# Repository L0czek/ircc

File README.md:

# Resonant Converter Controller

This repository contains a work-in-progress resonant converter controller project based on the STM32G474 microcontroller. The system splits responsibilities between the MCU (`controller`) and a host application (`host`) running on an x86 machine for configuration, logging, and waveform retrieval.

**Goals**
- Implement a phase-shifted resonant converter controller using the STM32G474 high-resolution timers.
- Provide over-current and other protections using built-in ADCs and comparator peripherals.
- Log waveforms to local SRAM for later retrieval by the host.
- Provide a PC-side host binary to configure and interact with the MCU.

Repository layout
- [controller](controller): MCU firmware (STM32 HAL-based). Core control logic lives here.
- [host](host): Host-side application that communicates with the MCU (x86 binary).
- [target](target): CubeMX / board-specific projects and HAL integration for different targets/boards.
- [pcb](pcb): KiCad PCB design files for the controller hardware.
- [protocol](protocol): Protocol definitions and protobufs used by host/MCU.
- [external](external): Third-party libraries and dependencies (e.g., nanpb, drivers).
- [build](build): Top-level build artifacts and CMake cache (generated during builds).

Quick start

Build host part (x86):

1. Enter the host directory and create a build directory:

```bash
cd host
mkdir -p build && cd build
cmake ..
make -j
```

The produced host binary will be in `host/build` (or as specified by the host CMakeLists).

Build MCU firmware:

1. Edit or inspect the CubeMX project in the appropriate `target/*` folder (for your chosen board). Generate code from CubeMX if you modify pin/peripheral configuration.
2. Use CMake from the top-level CMake to build the firmware. Example (from project root):

```bash
mkdir -p build-mcu && cd build-mcu
cmake -DCMAKE_TOOLCHAIN_FILE=cmake/gcc-arm-none-eabi.cmake ..
make -j
```

Flashing and debugging
- An OpenOCD config is available at `build/openocd.cfg` for target debugging.
- Typical workflow using the repository make targets:

	1. Start OpenOCD to provide the debug server:

		 ```bash
		 make openocd
		 ```

	2. In a separate terminal, flash or debug the firmware:

		 - To flash and run the firmware:

			 ```bash
			 make run
			 ```

		 - To spawn `gdb` for interactive debugging (connects to the OpenOCD server):

			 ```bash
			 make gdb
			 ```

- Or use your preferred OpenOCD/ST-Link workflow if you have a different setup.

Protocol and message formats
- Communication between host and MCU uses a UART serial link and the message definitions in the [protocol](protocol) directory (protobuf/nanopb). Regenerate or inspect generated code if you change `.proto` files.

Design notes
- The controller firmware uses the STM32G474 high-resolution timers to implement phase-shift control for MOSFET/IGBT bridge switching.
- ADCs, comparators, and timers are used for protections, sampling, and logging to SRAM.

Acknowledgements
- Third-party libraries are located in `external/` — see their respective LICENSE files for details.

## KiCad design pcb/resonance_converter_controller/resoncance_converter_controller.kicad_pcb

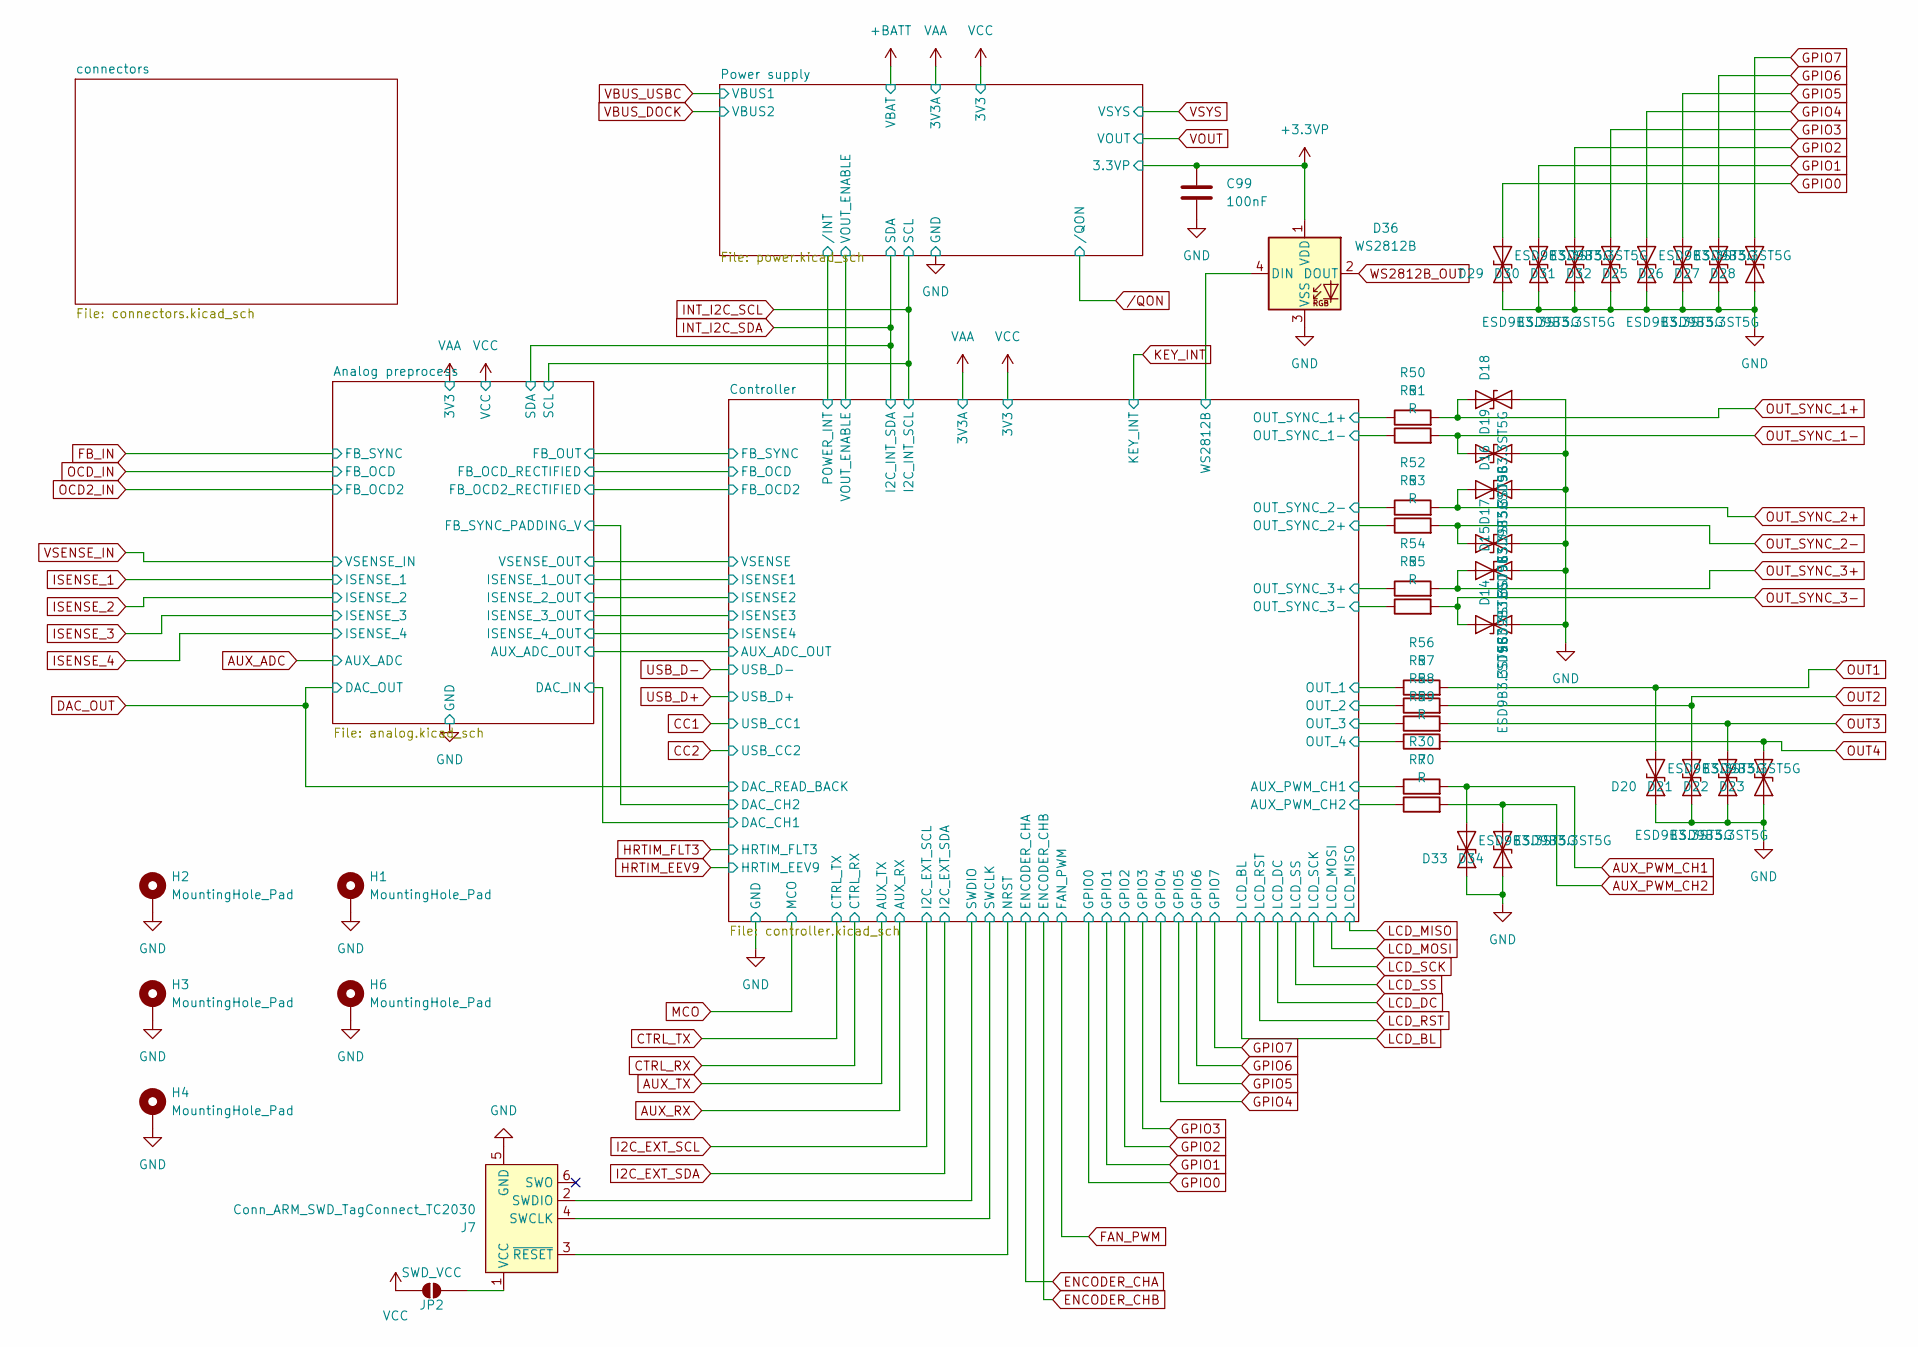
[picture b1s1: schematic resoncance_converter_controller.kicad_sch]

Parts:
C99: 100nF; C_0402_1005Metric
D14, D15, D16, D17, D18, D19, D20, D21, D22, D23, D25, D26, D27, D28, D29, D30, D31, D32, D33, D34: ESD9B3.3ST5G; D_SOD-923
D36: WS2812B; LED_WS2812B-Mini_PLCC4_3.5x3.5mm
H1, H2, H3, H4, H6: MountingHole_Pad; MountingHole_2.2mm_M2_Pad_Via
J7: Conn_ARM_SWD_TagConnect_TC2030; Tag-Connect_TC2030-IDC-FP_2x03_P1.27mm_Vertical
JP2: SWD_VCC; SolderJumper-2_P1.3mm_Open_RoundedPad1.0x1.5mm
R30, R50, R51, R52, R53, R54, R55, R56, R57, R58, R59, R70: R; R_0402_1005Metric

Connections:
+3.3VP: C99.1, D36.1 (VDD); also elsewhere on the board
/Controller/AUX_PWM_CH1: R30.1; also elsewhere on the board
/Controller/AUX_PWM_CH2: R70.1; also elsewhere on the board
/Controller/OUT_1: R56.1; also elsewhere on the board
/Controller/OUT_2: R57.1; also elsewhere on the board
/Controller/OUT_3: R58.1; also elsewhere on the board
/Controller/OUT_4: R59.1; also elsewhere on the board
/Controller/OUT_SYNC_1+: R50.1; also elsewhere on the board
/Controller/OUT_SYNC_1-: R51.1; also elsewhere on the board
/Controller/OUT_SYNC_2+: R53.1; also elsewhere on the board
/Controller/OUT_SYNC_2-: R52.1; also elsewhere on the board
/Controller/OUT_SYNC_3+: R54.1; also elsewhere on the board
/Controller/OUT_SYNC_3-: R55.1; also elsewhere on the board
/Controller/WS2812B: D36.4 (DIN); also elsewhere on the board
AUX_PWM_CH1: D33.1 (A1), R30.2; also elsewhere on the board
AUX_PWM_CH2: D34.1 (A1), R70.2; also elsewhere on the board
GND: C99.2, D14.1 (A1), D15.1 (A1), D16.1 (A1), D17.1 (A1), D18.1 (A1), D19.1 (A1), D20.2 (A2), D21.2 (A2), D22.2 (A2), D23.2 (A2), D25.2 (A2), D26.2 (A2), D27.2 (A2), D28.2 (A2), D29.2 (A2), D30.2 (A2), D31.2 (A2), D32.2 (A2), D33.2 (A2), D34.2 (A2), D36.3 (VSS), H1.1 (1_1), H2.1 (1_1), H3.1 (1_1), H4.1 (1_1), H6.1 (1_1), J7.5 (GND); also elsewhere on the board
GPIO0: D29.1 (A1); also elsewhere on the board
GPIO1: D30.1 (A1); also elsewhere on the board
GPIO2: D31.1 (A1); also elsewhere on the board
GPIO3: D32.1 (A1); also elsewhere on the board
GPIO4: D25.1 (A1); also elsewhere on the board
GPIO5: D26.1 (A1); also elsewhere on the board
GPIO6: D27.1 (A1); also elsewhere on the board
GPIO7: D28.1 (A1); also elsewhere on the board
NRST: J7.3 (~RESET); also elsewhere on the board
unnamed: J7.1 (VCC), JP2.2 (B)
OUT1: D20.1 (A1), R56.2; also elsewhere on the board
OUT2: D21.1 (A1), R57.2; also elsewhere on the board
OUT3: D22.1 (A1), R58.2; also elsewhere on the board
OUT4: D23.1 (A1), R59.2; also elsewhere on the board
OUT_SYNC_1+: D18.2 (A2), R50.2; also elsewhere on the board
OUT_SYNC_1-: D19.2 (A2), R51.2; also elsewhere on the board
OUT_SYNC_2+: D16.2 (A2), R52.2; also elsewhere on the board
OUT_SYNC_2-: D17.2 (A2), R53.2; also elsewhere on the board
OUT_SYNC_3+: D15.2 (A2), R54.2; also elsewhere on the board
OUT_SYNC_3-: D14.2 (A2), R55.2; also elsewhere on the board
SWCLK: J7.4 (SWCLK); also elsewhere on the board
SWDIO: J7.2 (SWDIO); also elsewhere on the board
VCC: JP2.1 (A); also elsewhere on the board
WS2812B_OUT: D36.2 (DOUT); also elsewhere on the board

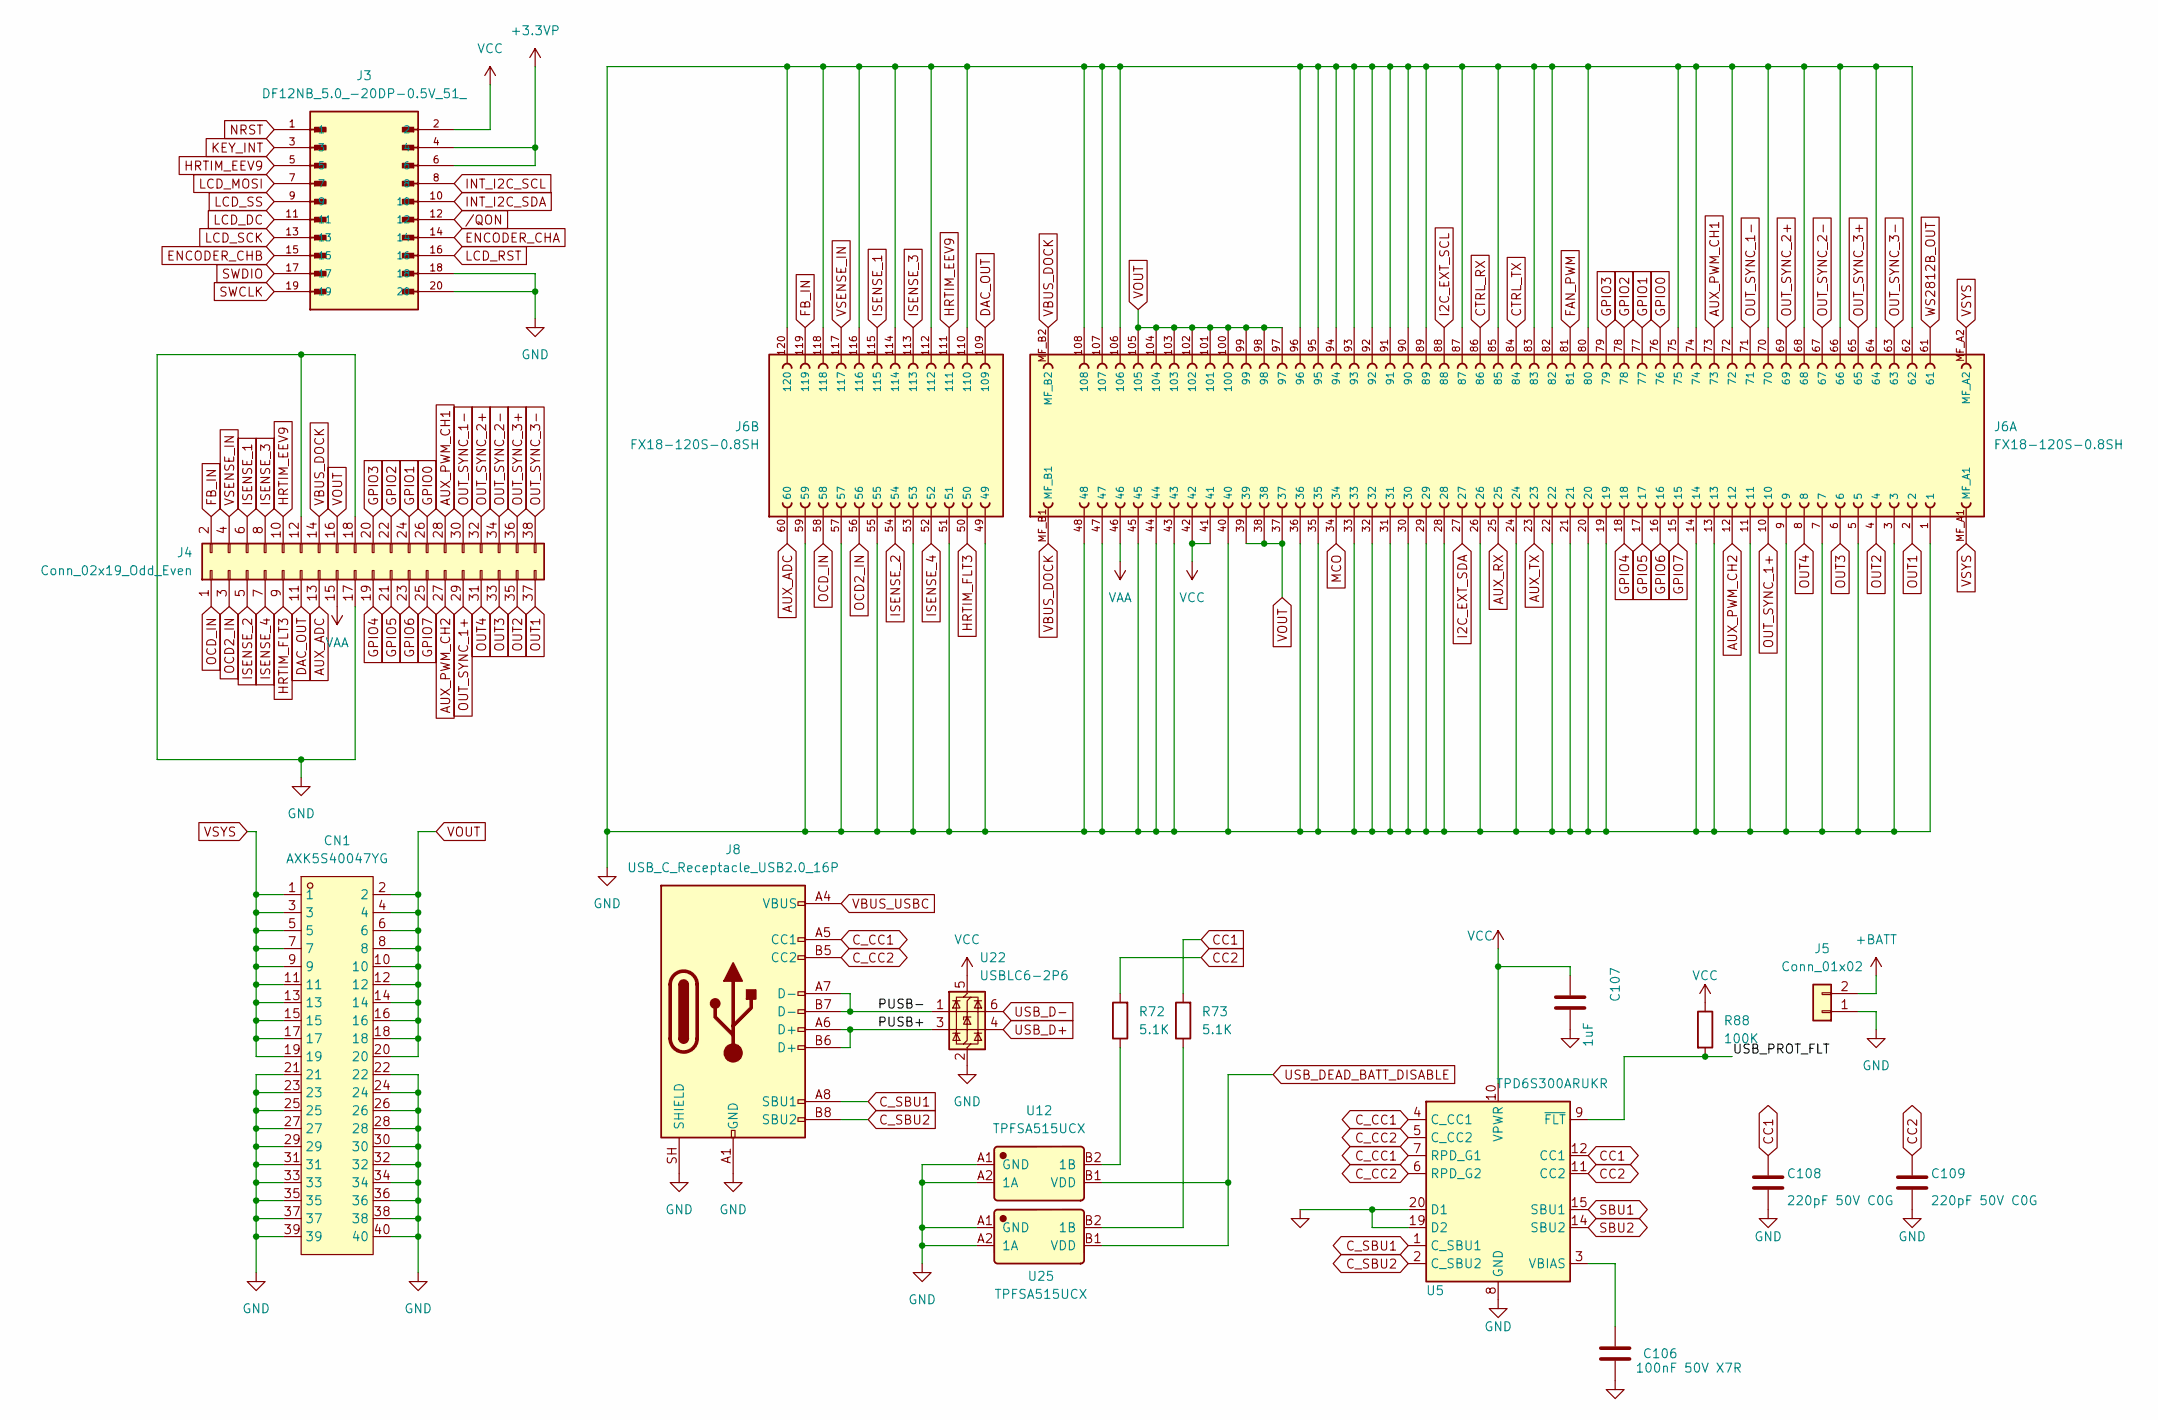
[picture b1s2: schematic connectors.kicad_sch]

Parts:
C106: 100nF 50V X7R; C_0603_1608Metric
C107: 1uF; C_0402_1005Metric
C108, C109: 220pF 50V C0G; C_0402_1005Metric
CN1: AXK5S40047YG; CONN-SMD_40P-P0.50_AXK5S40047YG; LCSC Part C3647996
J3: DF12NB_5.0_-20DP-0.5V_51_; HRS_DF12NB_5.0_-20DP-0.5V_51_
J4: Conn_02x19_Odd_Even; PinSocket_2x19_P2.54mm_Vertical_SMD
J5: Conn_01x02; AMASS_XT30U-M_1x02_P5.0mm_Vertical
J6: FX18-120S-0.8SH; HIROSE_FX18-120S-0.8SH; PARTREV 1
J8: USB_C_Receptacle_USB2.0_16P; USB_C_Receptacle_GCT_USB4105-xx-A_16P_TopMnt_Horizontal
R72, R73: 5.1K; R_0402_1005Metric
R88: 100K; R_0402_1005Metric
U5: TPD6S300ARUKR; Texas_RUK0020B_WQFN-20-1EP_3x3mm_P0.4mm_EP1.7x1.7mm_Thermal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
U12, U25: TPFSA515UCX; Manufacturer Part TPFSA515UCX; LCSC C52145990
U22: USBLC6-2P6; SOT-666

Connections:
+3.3VP: J3.4, J3.6; also elsewhere on the board
+BATT: J5.2; also elsewhere on the board
/connectors/PUSB+: J8.A6 (D+), J8.B6 (D+), U22.3 (I/O2)
/connectors/PUSB-: J8.A7 (D-), J8.B7 (D-), U22.1 (I/O1)
/connectors/USB_PROT_FLT: R88.2, U5.9 (~FLT)
AUX_ADC: J4.13, J6.60; also elsewhere on the board
AUX_PWM_CH1: J4.28, J6.73; also elsewhere on the board
AUX_PWM_CH2: J4.27, J6.12; also elsewhere on the board
AUX_RX: J6.25; also elsewhere on the board
AUX_TX: J6.23; also elsewhere on the board
CC1: C108.1, R73.2, U5.12 (CC1); also elsewhere on the board
CC2: C109.1, R72.2, U5.11 (CC2); also elsewhere on the board
CTRL_RX: J6.86; also elsewhere on the board
CTRL_TX: J6.84; also elsewhere on the board
C_CC1: J8.A5 (CC1), U5.4 (C_CC1), U5.7 (RPD_G1)
C_CC2: J8.B5 (CC2), U5.5 (C_CC2), U5.6 (RPD_G2)
C_SBU1: J8.A8 (SBU1), U5.1 (C_SBU1)
C_SBU2: J8.B8 (SBU2), U5.2 (C_SBU2)
DAC_OUT: J4.11, J6.109; also elsewhere on the board
ENCODER_CHA: J3.14; also elsewhere on the board
ENCODER_CHB: J3.15; also elsewhere on the board
FAN_PWM: J6.81; also elsewhere on the board
FB_IN: J4.2, J6.119; also elsewhere on the board
GND: C106.2, C107.2, C108.2, C109.2, CN1.21, CN1.22, CN1.23, CN1.24, CN1.25, CN1.26, CN1.27, CN1.28, CN1.29, CN1.30, CN1.31, CN1.32, CN1.33, CN1.34, CN1.35, CN1.36, CN1.37, CN1.38, CN1.39, CN1.40, J3.18, J3.20, J4.12, J4.17, J4.18, J5.1, J6.1, J6.3, J6.5, J6.7, J6.9, J6.11, J6.13, J6.14, J6.19, J6.20, J6.21, J6.22, J6.24, J6.26, J6.28, J6.29, J6.30, J6.31, J6.32, J6.33, J6.35, J6.36, J6.40, J6.43, J6.44, J6.45, J6.47, J6.48, J6.49, J6.51, J6.53, J6.55, J6.57, J6.59, J6.62, J6.64, J6.66, J6.68, J6.70, J6.72, J6.74, J6.75, J6.80, J6.82, J6.83, J6.85, J6.87, J6.89, J6.90, J6.91, J6.92, J6.93, J6.94, J6.95, J6.96, J6.106, J6.107, J6.108, J6.110, J6.112, J6.114, J6.116, J6.118, J6.120, J8.A1 (GND), J8.A12 (GND), J8.B1 (GND), J8.B12 (GND), J8.SH (SHIELD), U5.8 (GND), U5.13 (GND), U5.16 (GND), U5.17 (GND), U5.18 (GND), U5.19 (D2), U5.20 (D1), U5.21 (GND), U12.A1 (GND), U12.A2 (1A), U22.2 (GND), U25.A1 (GND), U25.A2 (1A); also elsewhere on the board
GPIO0: J4.26, J6.76; also elsewhere on the board
GPIO1: J4.24, J6.77; also elsewhere on the board
GPIO2: J4.22, J6.78; also elsewhere on the board
GPIO3: J4.20, J6.79; also elsewhere on the board
GPIO4: J4.19, J6.18; also elsewhere on the board
GPIO5: J4.21, J6.17; also elsewhere on the board
GPIO6: J4.23, J6.16; also elsewhere on the board
GPIO7: J4.25, J6.15; also elsewhere on the board
HRTIM_EEV9: J3.5, J4.10, J6.111; also elsewhere on the board
HRTIM_FLT3: J4.9, J6.50; also elsewhere on the board
I2C_EXT_SCL: J6.88; also elsewhere on the board
I2C_EXT_SDA: J6.27; also elsewhere on the board
INT_I2C_SCL: J3.8; also elsewhere on the board
INT_I2C_SDA: J3.10; also elsewhere on the board
ISENSE_1: J4.6, J6.115; also elsewhere on the board
ISENSE_2: J4.5, J6.54; also elsewhere on the board
ISENSE_3: J4.8, J6.113; also elsewhere on the board
ISENSE_4: J4.7, J6.52; also elsewhere on the board
KEY_INT: J3.3; also elsewhere on the board
LCD_DC: J3.11; also elsewhere on the board
LCD_MOSI: J3.7; also elsewhere on the board
LCD_RST: J3.16; also elsewhere on the board
LCD_SCK: J3.13; also elsewhere on the board
LCD_SS: J3.9; also elsewhere on the board
MCO: J6.34; also elsewhere on the board
NRST: J3.1; also elsewhere on the board
unnamed: C106.1, U5.3 (VBIAS)
unnamed: R72.1, U12.B2 (1B)
unnamed: R73.1, U25.B2 (1B)
OCD2_IN: J4.3, J6.56; also elsewhere on the board
OCD_IN: J4.1, J6.58; also elsewhere on the board
OUT1: J4.37, J6.2; also elsewhere on the board
OUT2: J4.35, J6.4; also elsewhere on the board
OUT3: J4.33, J6.6; also elsewhere on the board
OUT4: J4.31, J6.8; also elsewhere on the board
OUT_SYNC_1+: J4.29, J6.10; also elsewhere on the board
OUT_SYNC_1-: J4.30, J6.71; also elsewhere on the board
OUT_SYNC_2+: J4.32, J6.69; also elsewhere on the board
OUT_SYNC_2-: J4.34, J6.67; also elsewhere on the board
OUT_SYNC_3+: J4.36, J6.65; also elsewhere on the board
OUT_SYNC_3-: J4.38, J6.63; also elsewhere on the board
SBU1: U5.15 (SBU1); also elsewhere on the board
SBU2: U5.14 (SBU2); also elsewhere on the board
SWCLK: J3.19; also elsewhere on the board
SWDIO: J3.17; also elsewhere on the board
USB_D+: U22.4 (I/O2); also elsewhere on the board
USB_D-: U22.6 (I/O1); also elsewhere on the board
USB_DEAD_BATT_DISABLE: U12.B1 (VDD), U25.B1 (VDD); also elsewhere on the board
VAA: J4.15, J6.46; also elsewhere on the board
VBUS_DOCK: J4.14, J6.MF_B1, J6.MF_B2; also elsewhere on the board
VBUS_USBC: J8.A4 (VBUS), J8.A9 (VBUS), J8.B4 (VBUS), J8.B9 (VBUS); also elsewhere on the board
VCC: C107.1, J3.2, J6.41, J6.42, R88.1, U5.10 (VPWR), U22.5 (VBUS); also elsewhere on the board
VOUT: CN1.2, CN1.4, CN1.6, CN1.8, CN1.10, CN1.12, CN1.14, CN1.16, CN1.18, CN1.20, J4.16, J6.37, J6.38, J6.39, J6.97, J6.98, J6.99, J6.100, J6.101, J6.102, J6.103, J6.104, J6.105; also elsewhere on the board
VSENSE_IN: J4.4, J6.117; also elsewhere on the board
VSYS: CN1.1, CN1.3, CN1.5, CN1.7, CN1.9, CN1.11, CN1.13, CN1.15, CN1.17, CN1.19, J6.MF_A1, J6.MF_A2; also elsewhere on the board
WS2812B_OUT: J6.61; also elsewhere on the board
/QON: J3.12; also elsewhere on the board

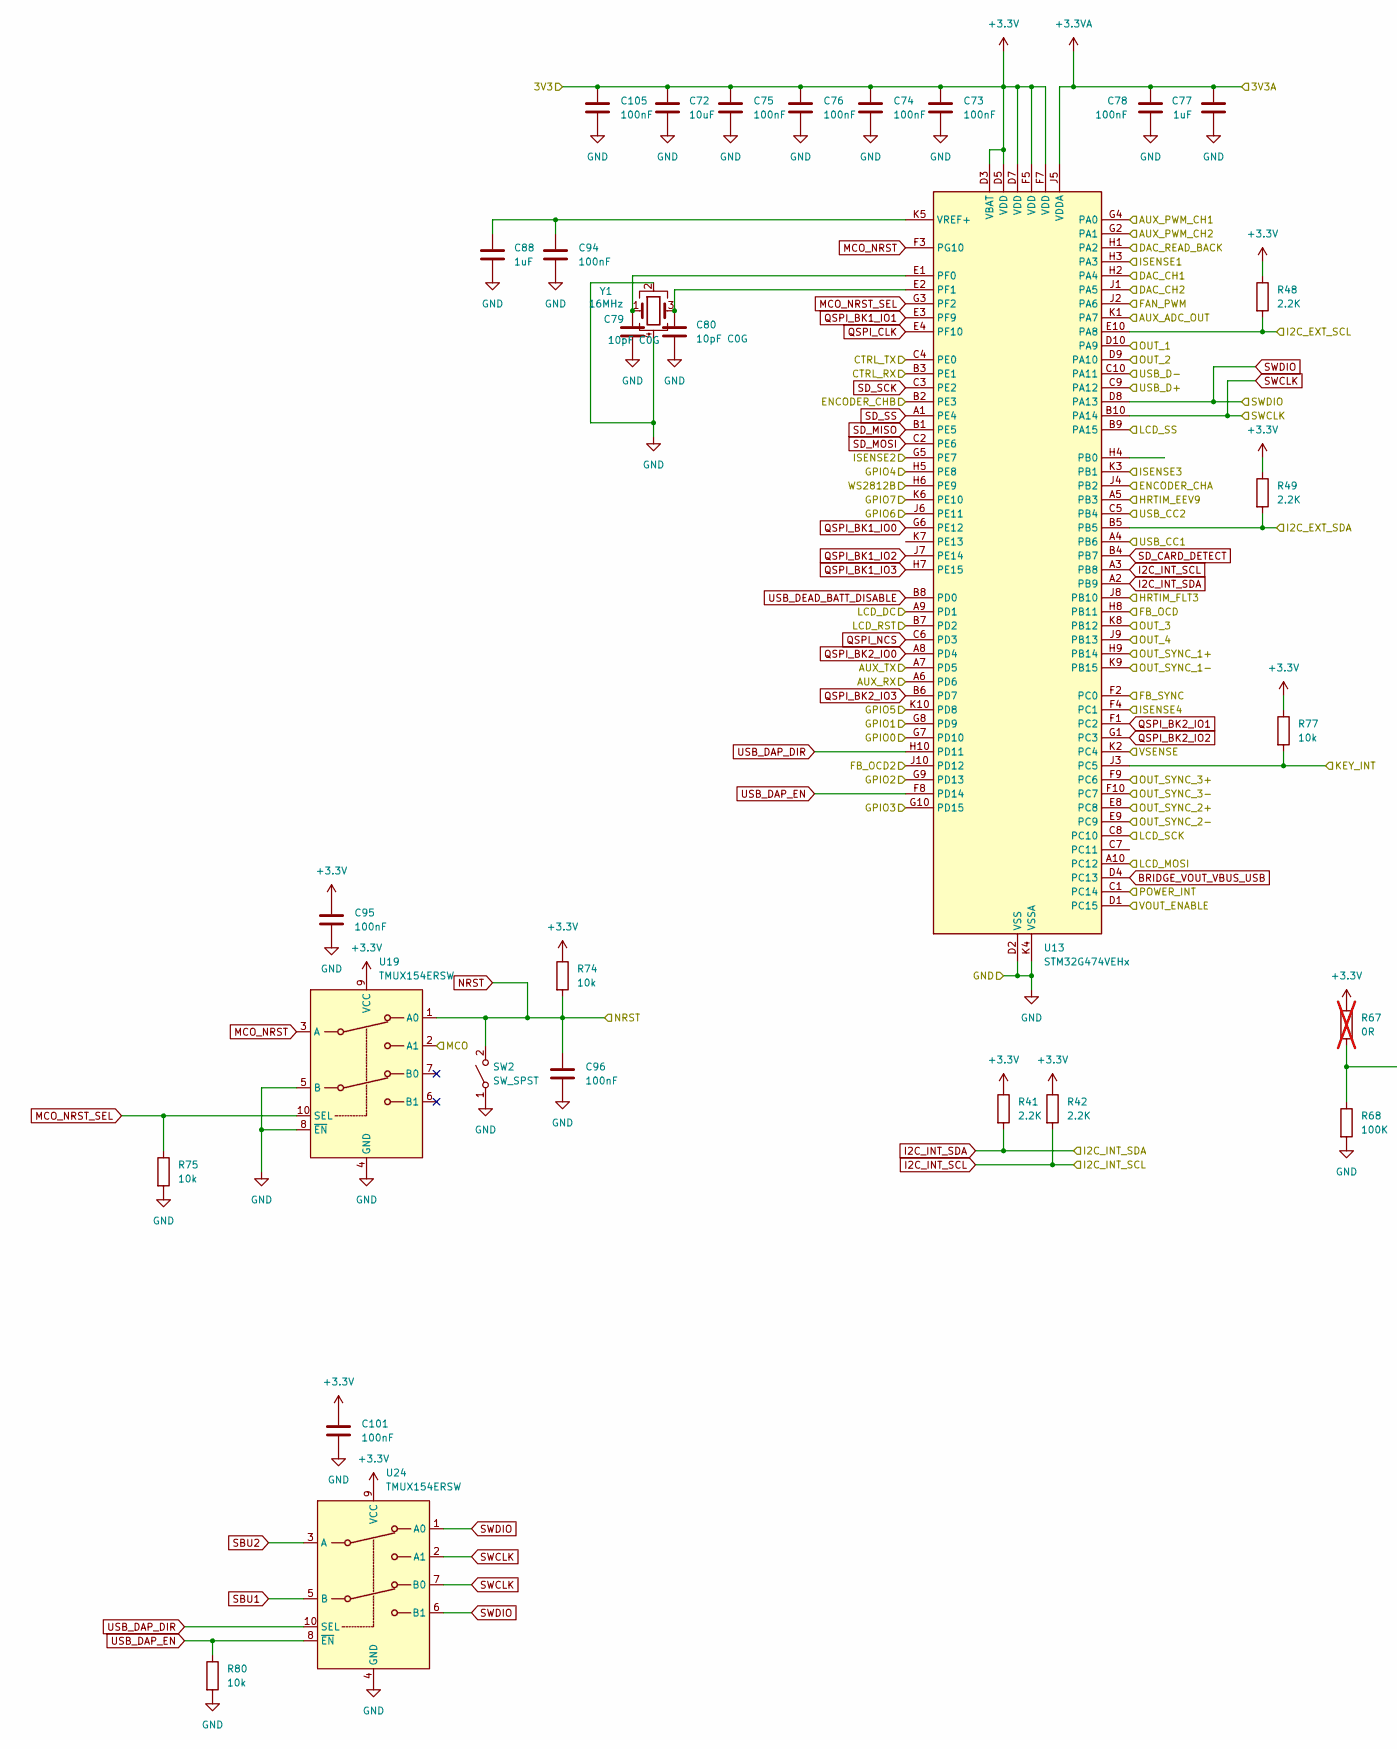
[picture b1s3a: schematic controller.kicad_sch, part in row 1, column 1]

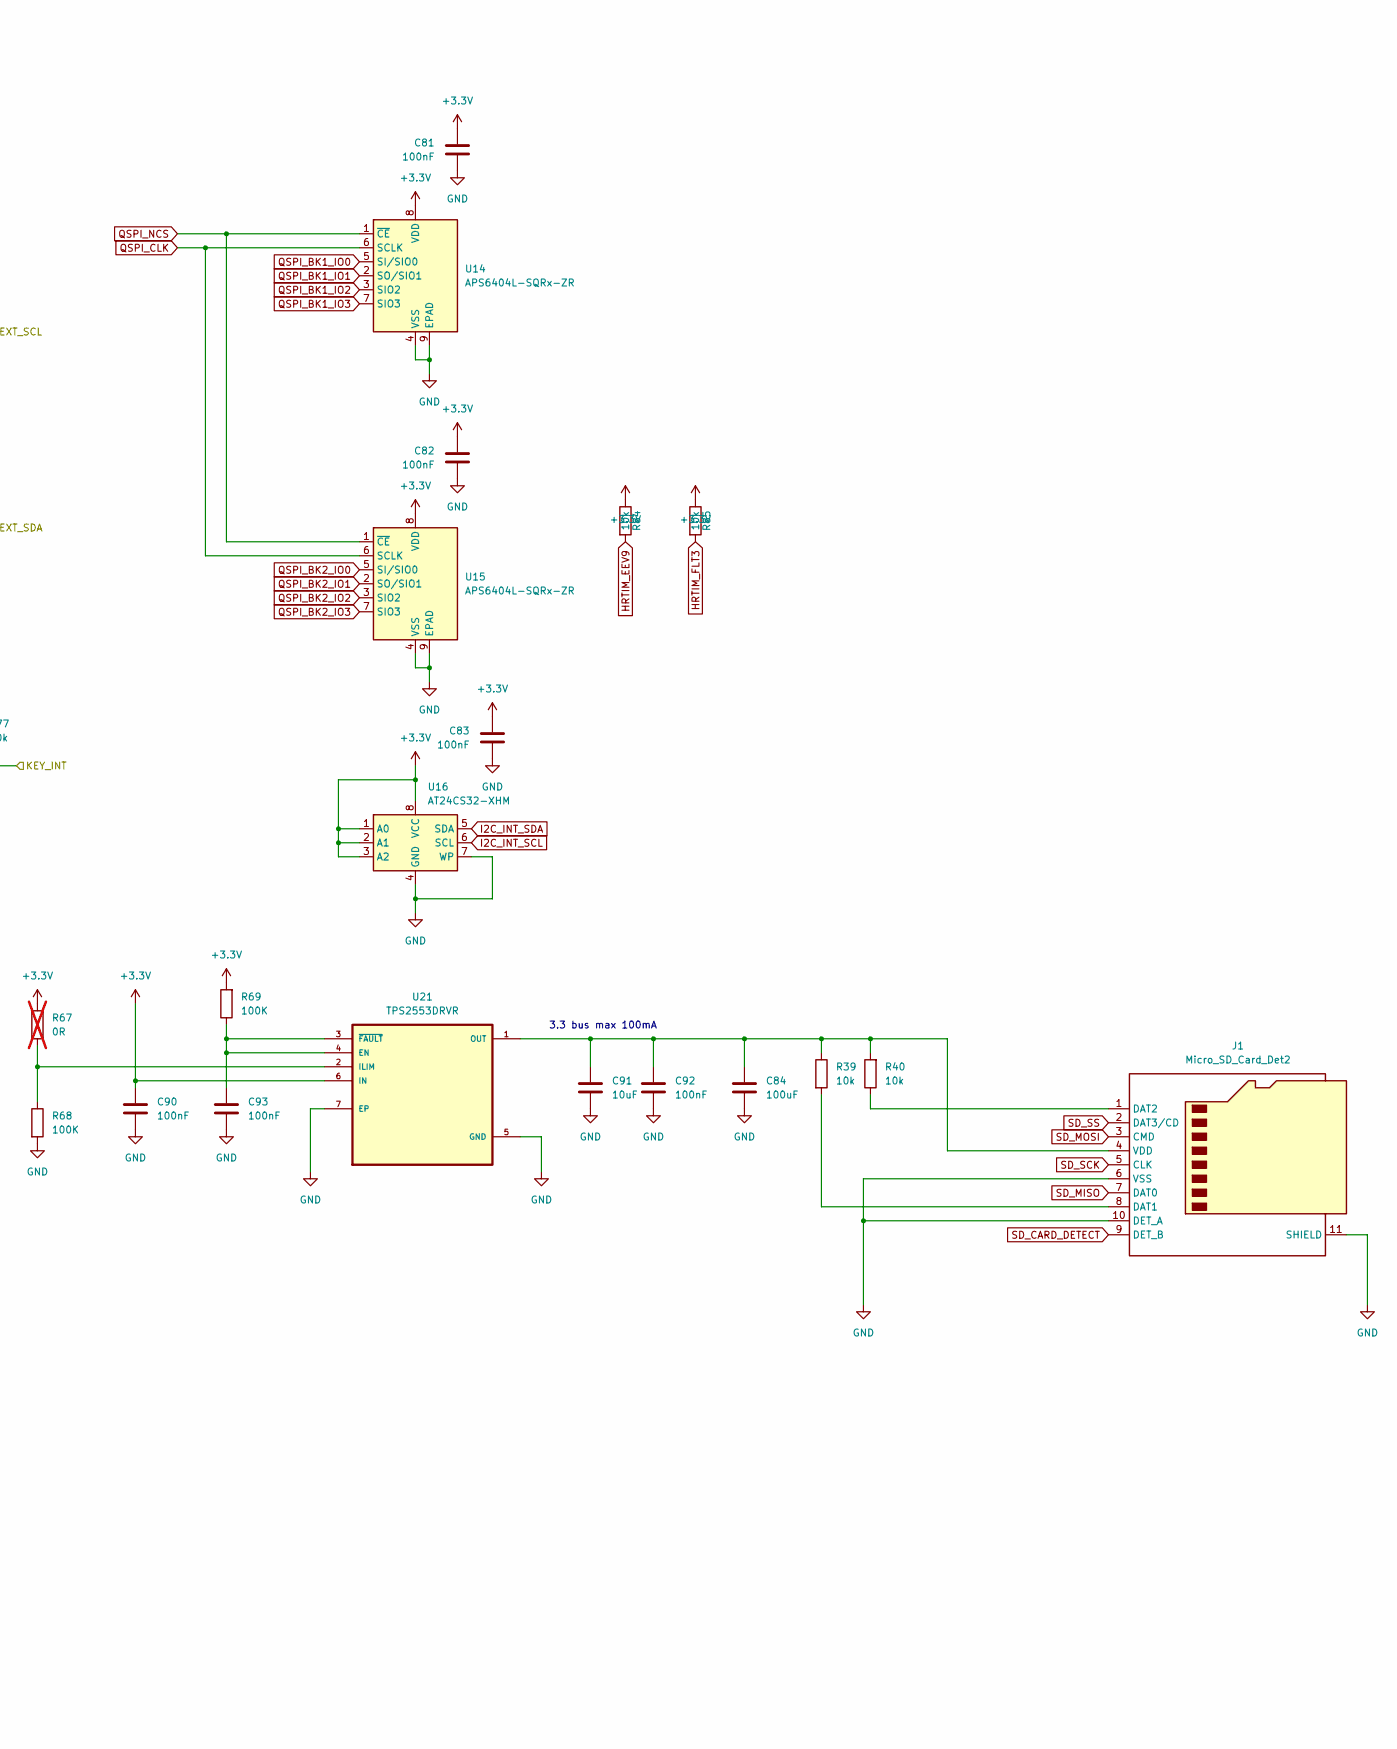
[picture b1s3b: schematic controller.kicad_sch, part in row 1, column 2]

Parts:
C72: 10uF; C_0805_2012Metric
C73, C74, C75, C76, C78, C81, C82, C83, C90, C92, C93, C94, C95, C96, C101, C105: 100nF; C_0402_1005Metric
C77: 1uF; C_0603_1608Metric
C79, C80: 10pF C0G; C_0402_1005Metric; MPN CL05C100JB5NNNC; LCSC C32949
C84: 100uF; C_1206_3216Metric
C88: 1uF; C_0402_1005Metric
C91: 10uF; C_1206_3216Metric
J1: Micro_SD_Card_Det2; microSD_HC_Hirose_DM3BT-DSF-PEJS
R39, R40, R74, R75, R77, R80, R84, R85: 10k; R_0402_1005Metric
R41, R42, R48, R49: 2.2K; R_0402_1005Metric
R67: 0R; R_0402_1005Metric; not fitted
R68, R69: 100K; R_0402_1005Metric
SW2: SW_SPST; SW_SPST_EVQPE1
U13: STM32G474VEHx; TFBGA-100_8x8mm_Layout10x10_P0.8mm
U14, U15: APS6404L-SQRx-ZR; Winbond_USON-8-1EP_3x2mm_P0.5mm_EP0.2x1.6mm
U16: AT24CS32-XHM; TSSOP-8_4.4x3mm_P0.65mm
U19, U24: TMUX154ERSW; UQFN-10_1.4x1.8mm_P0.4mm
U21: TPS2553DRVR; SON65P200X200X80-7N
Y1: 16MHz; Crystal_SMD_3225-4Pin_3.2x2.5mm; MPN X322516MLB4SI; LCSC C13738

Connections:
/Analog preprocess/DAC_IN: U13.H2 (PA4); also elsewhere on the board
/Analog preprocess/FB_OCD2_RECTIFIED: U13.J10 (PD12); also elsewhere on the board
/Analog preprocess/FB_OCD_RECTIFIED: U13.H8 (PB11); also elsewhere on the board
/Analog preprocess/FB_OUT: U13.F2 (PC0); also elsewhere on the board
/Analog preprocess/FB_SYNC_PADDING_V: U13.J1 (PA5); also elsewhere on the board
/Analog preprocess/ISENSE_1_OUT: U13.H3 (PA3); also elsewhere on the board
/Analog preprocess/ISENSE_2_OUT: U13.G5 (PE7); also elsewhere on the board
/Analog preprocess/ISENSE_3_OUT: U13.K3 (PB1); also elsewhere on the board
/Analog preprocess/ISENSE_4_OUT: U13.F4 (PC1); also elsewhere on the board
/Analog preprocess/VSENSE_OUT: U13.K2 (PC4); also elsewhere on the board
/Controller/AUX_PWM_CH1: U13.G4 (PA0); also elsewhere on the board
/Controller/AUX_PWM_CH2: U13.G2 (PA1); also elsewhere on the board
/Controller/OUT_1: U13.D10 (PA9); also elsewhere on the board
/Controller/OUT_2: U13.D9 (PA10); also elsewhere on the board
/Controller/OUT_3: U13.K8 (PB12); also elsewhere on the board
/Controller/OUT_4: U13.J9 (PB13); also elsewhere on the board
/Controller/OUT_SYNC_1+: U13.H9 (PB14); also elsewhere on the board
/Controller/OUT_SYNC_1-: U13.K9 (PB15); also elsewhere on the board
/Controller/OUT_SYNC_2+: U13.E8 (PC8); also elsewhere on the board
/Controller/OUT_SYNC_2-: U13.E9 (PC9); also elsewhere on the board
/Controller/OUT_SYNC_3+: U13.F9 (PC6); also elsewhere on the board
/Controller/OUT_SYNC_3-: U13.F10 (PC7); also elsewhere on the board
/Controller/VOUT_ENABLE: U13.D1 (PC15); also elsewhere on the board
/Controller/WS2812B: U13.H6 (PE9); also elsewhere on the board
AUX_ADC: U13.K1 (PA7); also elsewhere on the board
AUX_RX: U13.A6 (PD6); also elsewhere on the board
AUX_TX: U13.A7 (PD5); also elsewhere on the board
BRIDGE_VOUT_VBUS_USB: U13.D4 (PC13); also elsewhere on the board
CC1: U13.A4 (PB6); also elsewhere on the board
CC2: U13.C5 (PB4); also elsewhere on the board
CTRL_RX: U13.B3 (PE1); also elsewhere on the board
CTRL_TX: U13.C4 (PE0); also elsewhere on the board
DAC_OUT: U13.H1 (PA2); also elsewhere on the board
ENCODER_CHA: U13.J4 (PB2); also elsewhere on the board
ENCODER_CHB: U13.B2 (PE3); also elsewhere on the board
FAN_PWM: U13.J2 (PA6); also elsewhere on the board
GND: C72.2, C73.2, C74.2, C75.2, C76.2, C77.2, C78.2, C79.2, C80.2, C81.2, C82.2, C83.2, C84.2, C88.2, C90.2, C91.2, C92.2, C93.2, C94.2, C95.2, C96.2, C101.2, C105.2, J1.6 (VSS), J1.10 (DET_A), J1.11 (SHIELD), R68.2, R75.2, R80.2, SW2.1 (A), U13.D2 (VSS), U13.D6 (VSS), U13.E5 (VSS), U13.E6 (VSS), U13.E7 (VSS), U13.F6 (VSS), U13.K4 (VSSA), U14.4 (VSS), U14.9 (EPAD), U15.4 (VSS), U15.9 (EPAD), U16.4 (GND), U16.7 (WP), U19.4 (GND), U19.5 (B), U19.8 (~EN), U21.5 (GND), U21.7 (EP), U24.4 (GND), Y1.2, Y1.4; also elsewhere on the board
GPIO0: U13.G7 (PD10); also elsewhere on the board
GPIO1: U13.G8 (PD9); also elsewhere on the board
GPIO2: U13.G9 (PD13); also elsewhere on the board
GPIO3: U13.G10 (PD15); also elsewhere on the board
GPIO4: U13.H5 (PE8); also elsewhere on the board
GPIO5: U13.K10 (PD8); also elsewhere on the board
GPIO6: U13.J6 (PE11); also elsewhere on the board
GPIO7: U13.K6 (PE10); also elsewhere on the board
HRTIM_EEV9: R84.2, U13.A5 (PB3); also elsewhere on the board
HRTIM_FLT3: R85.2, U13.J8 (PB10); also elsewhere on the board
I2C_EXT_SCL: R48.2, U13.E10 (PA8); also elsewhere on the board
I2C_EXT_SDA: R49.2, U13.B5; also elsewhere on the board
INT_I2C_SCL: R42.2, U13.A3 (PB8), U16.6 (SCL); also elsewhere on the board
INT_I2C_SDA: R41.2, U13.A2 (PB9), U16.5 (SDA); also elsewhere on the board
KEY_INT: R77.2, U13.J3 (PC5); also elsewhere on the board
LCD_DC: U13.A9 (PD1); also elsewhere on the board
LCD_MOSI: U13.A10 (PC12); also elsewhere on the board
LCD_RST: U13.B7 (PD2); also elsewhere on the board
LCD_SCK: U13.C8 (PC10); also elsewhere on the board
LCD_SS: U13.B9 (PA15); also elsewhere on the board
MCO: U19.2 (A1); also elsewhere on the board
MCO_NRST: U13.F3 (PG10), U19.3 (A)
MCO_NRST_SEL: R75.1, U13.G3 (PF2), U19.10 (SEL)
NRST: C96.1, R74.2, SW2.2 (B), U19.1 (A0); also elsewhere on the board
unnamed: J1.8 (DAT1), R39.2
unnamed: J1.1 (DAT2), R40.1
unnamed: C84.1, C91.1, C92.1, J1.4 (VDD), R39.1, R40.2, U21.1 (OUT)
unnamed: C79.1, U13.E1 (PF0), Y1.1
unnamed: C80.1, U13.E2 (PF1), Y1.3
unnamed: C88.1, C94.1, U13.K5 (VREF+)
unnamed: C93.1, R69.1, U21.3 (~FAULT), U21.4 (EN)
unnamed: R67.2, R68.1, U21.2 (ILIM)
QSPI_BK1_IO0: U13.G6 (PE12), U14.5 (SI/SIO0)
QSPI_BK1_IO1: U13.E3 (PF9), U14.2 (SO/SIO1)
QSPI_BK1_IO2: U13.J7 (PE14), U14.3 (SIO2)
QSPI_BK1_IO3: U13.H7 (PE15), U14.7 (SIO3)
QSPI_BK2_IO0: U13.A8 (PD4), U15.5 (SI/SIO0)
QSPI_BK2_IO1: U13.F1 (PC2), U15.2 (SO/SIO1)
QSPI_BK2_IO2: U13.G1 (PC3), U15.3 (SIO2)
QSPI_BK2_IO3: U13.B6 (PD7), U15.7 (SIO3)
QSPI_CLK: U13.E4 (PF10), U14.6 (SCLK), U15.6 (SCLK)
QSPI_NCS: U13.C6 (PD3), U14.1 (~CE), U15.1 (~CE)
SBU1: U24.5 (B); also elsewhere on the board
SBU2: U24.3 (A); also elsewhere on the board
SD_CARD_DETECT: J1.9 (DET_B), U13.B4 (PB7)
SD_MISO: J1.7 (DAT0), U13.B1 (PE5)
SD_MOSI: J1.3 (CMD), U13.C2 (PE6)
SD_SCK: J1.5 (CLK), U13.C3 (PE2)
SD_SS: J1.2 (DAT3/CD), U13.A1 (PE4)
SWCLK: U13.B10 (PA14), U24.2 (A1), U24.7 (B0); also elsewhere on the board
SWDIO: U13.D8 (PA13), U24.1 (A0), U24.6 (B1); also elsewhere on the board
USB_D+: U13.C9 (PA12); also elsewhere on the board
USB_D-: U13.C10 (PA11); also elsewhere on the board
USB_DAP_DIR: U13.H10 (PD11), U24.10 (SEL)
USB_DAP_EN: R80.1, U13.F8 (PD14), U24.8 (~EN)
USB_DEAD_BATT_DISABLE: U13.B8 (PD0); also elsewhere on the board
VAA: C77.1, C78.1, U13.J5 (VDDA); also elsewhere on the board
VCC: C72.1, C73.1, C74.1, C75.1, C76.1, C81.1, C82.1, C83.1, C90.1, C95.1, C101.1, C105.1, R41.1, R42.1, R48.1, R49.1, R67.1, R69.2, R74.1, R77.1, R84.1, R85.1, U13.D3 (VBAT), U13.D5 (VDD), U13.D7 (VDD), U13.F5 (VDD), U13.F7 (VDD), U14.8 (VDD), U15.8 (VDD), U16.1 (A0), U16.2 (A1), U16.3 (A2), U16.8 (VCC), U19.9 (VCC), U21.6 (IN), U24.9 (VCC); also elsewhere on the board
/INT: U13.C1 (PC14); also elsewhere on the board

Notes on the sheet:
3.3 bus max 100mA

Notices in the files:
target/resonant_converter_controller/Core/Src/main.c:
Copyright (c) 2025 STMicroelectronics.
All rights reserved.
This software is licensed under terms that can be found in the LICENSE file
parts and their libraries:
COPYRIGHT: Copyright C 2016 Accelerated Designs. All rights reserved
